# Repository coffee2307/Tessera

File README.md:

# Tessera

## English

### Overview

Tessera is a personal precision motion platform for compact XYZ positioning, alignment, probing, microscopy, and small-scale automation. It combines a parallel-kinematic mechanical structure with closed-loop stepper control, rotary encoders, motion planning, and a serial command interface.

The design aims to provide a low-cost and reproducible motion platform with practical sub-micron positioning capability for laboratory, research, and prototyping workflows. The software stack is divided between embedded firmware and a Python control layer so the hardware can be configured, calibrated, and operated through a clean API.

### Main features

- 3-axis XYZ motion using a parallel-kinematic mechanism
- Closed-loop control with stepper motors and encoder feedback
- Sub-micron positioning for precision alignment and inspection work
- USB serial communication with G-code-style command handling
- Firmware-side path planning and interpolation for smooth motion
- Homing and calibration routines for repeatable setup
- External tool control support for device actuation
- Open hardware and software structure for experimentation and customization

### Project architecture

The repository is organized into several functional domains:

- Mechanical design: CAD and manufacturing files in thiet_ke_co_khi/
- Electronics: PCB and schematics in dien_tu/
- Firmware: embedded C++ controller in phan_mem_nhung/bo_dieu_khien_chuyen_dong_rp/
- Python API: device communication and helper scripts in phan_mem/api_python/
- Documentation: build notes, setup guidance, and BOM in tai_lieu/

### Repository structure

- thiet_ke_co_khi/ - CAD models, assemblies, and mechanical parts
- dien_tu/ - KiCad PCB schematics and board files
- phan_mem_nhung/bo_dieu_khien_chuyen_dong_rp/ - firmware project and embedded source code
- phan_mem_nhung/bo_dieu_khien_chuyen_dong_rp/src/ - C++ firmware implementation
- phan_mem/api_python/ - Python API, utilities, and usage examples
- tai_lieu/ - technical documentation, setup references, and BOM

### Mechanical design

The mechanical platform uses a parallel geometry to achieve compact motion with high stiffness and repeatability. The structure is designed around a three-axis motion system, with linkage and ball-joint behavior tuned for controlled end-effector motion. Mechanical files are stored in the FreeCAD-based construction package and are intended to be modified and adapted for custom builds.

### Electronics design

The electronics layer includes the control board and related hardware configuration. The system relies on stepper drives, encoder interfaces, logic/control circuitry, and power distribution arranged to support the motion controller and its real-time feedback loops. These design files are located under dien_tu/ and provide the hardware reference for the embedded controller.

### Firmware architecture

The firmware is written in C++ and is organized around the real-time device controller. It implements the logic required for motion execution, servo regulation, calibration, and serial communication.

Core firmware responsibilities:

- Kinematic model: workspace and geometry calculations
- Motion controller: command execution and trajectory planning
- Servo control: feedback loops and actuator regulation
- Homing and calibration: initialization and system alignment
- Communication layer: command parsing and response handling

Main firmware components:

- phan_mem_nhung/bo_dieu_khien_chuyen_dong_rp/src/main.cpp - startup and system initialization
- phan_mem_nhung/bo_dieu_khien_chuyen_dong_rp/src/robot.cpp - coordinated device behavior
- phan_mem_nhung/bo_dieu_khien_chuyen_dong_rp/src/dieu_khien_chuyen_dong/ - path planning and movement logic
- phan_mem_nhung/bo_dieu_khien_chuyen_dong_rp/src/dieu_khien_servo/ - closed-loop control loops
- phan_mem_nhung/bo_dieu_khien_chuyen_dong_rp/src/mo_hinh_dong_hoc/ - geometry and kinematic calculations
- phan_mem_nhung/bo_dieu_khien_chuyen_dong_rp/src/hw_config.h - hardware configuration such as pin map and motor settings

### Control and communication model

The system is intended to be commanded over a serial connection. The firmware accepts motion and control instructions and returns status information to the host. This makes it compatible with higher-level control software, automation workflows, and Python-based experimentation.

Typical capabilities include:

- moving to target coordinates
- homing the axes
- enabling or disabling motors
- querying device state
- calibrating joints
- setting tool output values

### Python API

The Python layer wraps the serial connection and exposes a simplified interface for controlling the platform. It is intended to reduce the amount of low-level command handling required when testing motion, calibration, or automated procedures.

Relevant Python files:

- phan_mem/api_python/tessera_api.py
- phan_mem/api_python/vi_du_su_dung.py
- phan_mem/api_python/ve_bieu_do_hieu_chuan.py

The API generally supports:

- connection management
- homing and motion commands
- calibration routines
- device status queries
- asynchronous logging and communication feedback

### Quick start

1. Review the mechanical and electrical documentation in tai_lieu/.
2. Build the hardware according to the project instructions.
3. Adjust the hardware configuration in phan_mem_nhung/bo_dieu_khien_chuyen_dong_rp/src/hw_config.h.
4. Flash the firmware using PlatformIO.
5. Connect the device over serial.
6. Use the Python API or a terminal client to home the platform and begin motion testing.

### Example usage

```python
from phan_mem.api_python.tessera_api import TesseraInterface

api = TesseraInterface(show_communication=True, show_log_messages=True)
api.connect('/dev/ttyACM0')

api.home()
api.move_to(0.0, 0.0, 0.0, f=10)
api.move_to(3.1, 4.1, 5.9, f=26)
api.wait_for_stop()
```

### Notes

- The project is designed for open experimentation and reproducible builds.
- The firmware and mechanical system are the primary technical foundations of the repository.
- The Python layer is meant to simplify communication, testing, calibration, and operational workflows.

---

## Tiếng Việt

### Tổng quan

Tessera là một nền tảng chuyển động XYZ kiểu compact, mã nguồn mở, được thiết kế cho các nhiệm vụ căn chỉnh, dò kiểm tra, kính hiển vi và tự động hóa quy mô nhỏ. Hệ thống này kết hợp cơ cấu cơ khí song song, bộ điều khiển động cơ vòng kín, và giao diện điều khiển thân thiện với Python để tạo ra một giải pháp di chuyển chính xác với chi phí thấp và khả năng tái tạo tốt.

### Tính năng chính

- Chuyển động 3 trục XYZ theo cơ cấu song song
- Điều khiển vòng kín bằng động cơ bước và bộ mã hóa quay
- Khả năng định vị ở mức dưới micromet cho công việc căn chỉnh và kiểm tra
- Giao tiếp qua cổng serial USB với lệnh kiểu G-code
- Lập lịch đường đi và nội suy chuyển động ở phần firmware
- Chức năng homing và hiệu chuẩn để khởi tạo hệ thống lặp lại
- Hỗ trợ điều khiển đầu công cụ ngoài để kích hoạt thiết bị phụ trợ
- Cấu trúc phần cứng và phần mềm mở, dễ tùy biến và thử nghiệm

### Kiến trúc dự án

Kho mã nguồn được tổ chức theo các tầng chức năng chính:

- Thiết kế cơ khí: mô hình CAD và file gia công trong thiet_ke_co_khi/
- Điện tử: bo mạch và sơ đồ trong dien_tu/
- Firmware: bộ điều khiển nhúng C++ trong phan_mem_nhung/bo_dieu_khien_chuyen_dong_rp/
- Python API: giao tiếp thiết bị và script hỗ trợ trong phan_mem/api_python/
- Tài liệu: hướng dẫn xây dựng, thiết lập và BOM trong tai_lieu/

### Cấu trúc thư mục

- thiet_ke_co_khi/ - mô hình CAD, bộ lắp ráp và linh kiện cơ khí
- dien_tu/ - file sơ đồ PCB KiCad và board layout
- phan_mem_nhung/bo_dieu_khien_chuyen_dong_rp/ - mã nguồn firmware và dự án PlatformIO
- phan_mem_nhung/bo_dieu_khien_chuyen_dong_rp/src/ - phần triển khai firmware C++
- phan_mem/api_python/ - API Python, tiện ích và ví dụ sử dụng
- tai_lieu/ - tài liệu kỹ thuật, hướng dẫn lắp đặt và danh mục vật tư

### Thiết kế cơ khí

Cấu trúc cơ khí sử dụng hình học song song để đạt được chuyển động nhỏ gọn, cứng vững và lặp lại tốt. Hệ thống được thiết kế theo mô hình 3 trục với các liên kết và khớp cầu nhằm kiểm soát chuyển động của đầu công cụ. Các file thiết kế cơ khí nằm trong gói CAD FreeCAD và có thể được chỉnh sửa để phù hợp với từng bản dựng cụ thể.

### Thiết kế điện tử

Lớp điện tử bao gồm bo mạch điều khiển và cấu hình phần cứng tương ứng. Hệ thống dùng động cơ bước, giao diện mã hóa, mạch điều khiển logic và phân phối nguồn để hỗ trợ bộ điều khiển chuyển động và vòng phản hồi thời gian thực. Các file này nằm trong dien_tu/ và là tài liệu tham khảo cho phần firmware.

### Kiến trúc firmware

Firmware được viết bằng C++ và tổ chức theo mô hình bộ điều khiển thiết bị thời gian thực. Nó xử lý các nhiệm vụ cần thiết cho việc thực thi chuyển động, điều khiển servo, hiệu chuẩn và giao tiếp serial.

Các trách nhiệm chính của firmware:

- Mô hình động học: tính toán không gian làm việc và hình học
- Bộ điều khiển chuyển động: thực thi lệnh và lập kế hoạch quỹ đạo
- Điều khiển servo: vòng lặp phản hồi và điều chỉnh actuator
- Homing và hiệu chuẩn: khởi tạo và căn chỉnh hệ thống
- Lớp giao tiếp: phân tích lệnh và xử lý phản hồi

Những thành phần quan trọng:

- phan_mem_nhung/bo_dieu_khien_chuyen_dong_rp/src/main.cpp - khởi động và khởi tạo hệ thống
- phan_mem_nhung/bo_dieu_khien_chuyen_dong_rp/src/robot.cpp - hành vi tổng hợp của thiết bị
- phan_mem_nhung/bo_dieu_khien_chuyen_dong_rp/src/dieu_khien_chuyen_dong/ - logic lập kế hoạch đường đi
- phan_mem_nhung/bo_dieu_khien_chuyen_dong_rp/src/dieu_khien_servo/ - vòng lặp điều khiển đóng
- phan_mem_nhung/bo_dieu_khien_chuyen_dong_rp/src/mo_hinh_dong_hoc/ - tính toán hình học và động học
- phan_mem_nhung/bo_dieu_khien_chuyen_dong_rp/src/hw_config.h - cấu hình phần cứng như chân GPIO và cài đặt motor

### Mô hình điều khiển và truyền thông

Hệ thống được thiết kế để điều khiển qua kết nối serial. Firmware nhận lệnh di chuyển và điều khiển từ máy tính và gửi thông tin trạng thái trở lại. Điều này giúp hệ thống tương thích với phần mềm điều khiển cấp cao, quy trình tự động hóa và thử nghiệm dựa trên Python.

Các khả năng điển hình gồm:

- di chuyển đến tọa độ mục tiêu
- homing trục
- bật/tắt động cơ
- truy vấn trạng thái thiết bị
- hiệu chuẩn joint
- đặt giá trị đầu ra của công cụ

### Python API

Lớp Python đóng gói kết nối serial và cung cấp giao diện đơn giản để điều khiển hệ thống. Mục tiêu là giảm khối lượng xử lý lệnh mức thấp khi kiểm tra chuyển động, hiệu chuẩn hoặc quy trình tự động hóa.

Các file Python quan trọng:

- phan_mem/api_python/tessera_api.py
- phan_mem/api_python/vi_du_su_dung.py
- phan_mem/api_python/ve_bieu_do_hieu_chuan.py

API thường hỗ trợ:

- quản lý kết nối
- lệnh homing và di chuyển
- chức năng hiệu chuẩn
- truy vấn trạng thái thiết bị
- log giao tiếp và phản hồi liên tục

### Bắt đầu nhanh

1. Đọc tài liệu cơ khí và điện tử trong tai_lieu/
2. Lắp ráp phần cứng theo hướng dẫn của dự án
3. Điều chỉnh cấu hình phần cứng trong phan_mem_nhung/bo_dieu_khien_chuyen_dong_rp/src/hw_config.h
4. Nạp firmware bằng PlatformIO
5. Kết nối thiết bị qua serial
6. Dùng Python API hoặc client terminal để homing trục và bắt đầu kiểm tra chuyển động

### Ví dụ sử dụng

```python
from phan_mem.api_python.tessera_api import TesseraInterface

api = TesseraInterface(show_communication=True, show_log_messages=True)
api.connect('/dev/ttyACM0')

api.home()
api.move_to(0.0, 0.0, 0.0, f=10)
api.move_to(3.1, 4.1, 5.9, f=26)
api.wait_for_stop()
```

### Lưu ý

- Dự án này thích hợp cho thử nghiệm mở và bản dựng có thể tái sản xuất.
- Firmware và hệ thống cơ khí là nền tảng kỹ thuật chính của kho mã nguồn.
- Lớp Python nhằm đơn giản hóa giao tiếp, thử nghiệm, hiệu chuẩn và quy trình vận hành.

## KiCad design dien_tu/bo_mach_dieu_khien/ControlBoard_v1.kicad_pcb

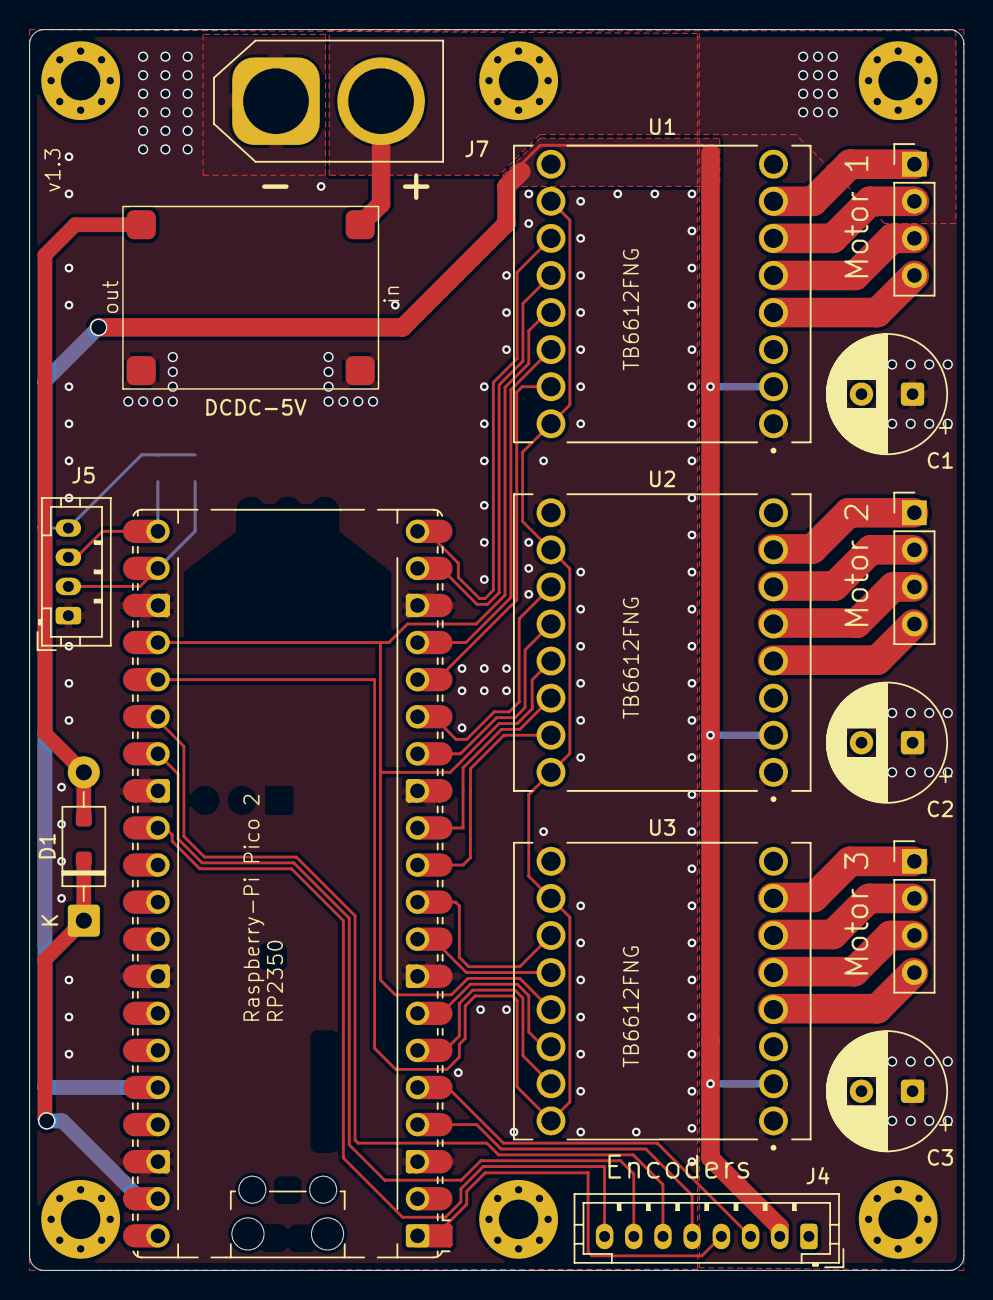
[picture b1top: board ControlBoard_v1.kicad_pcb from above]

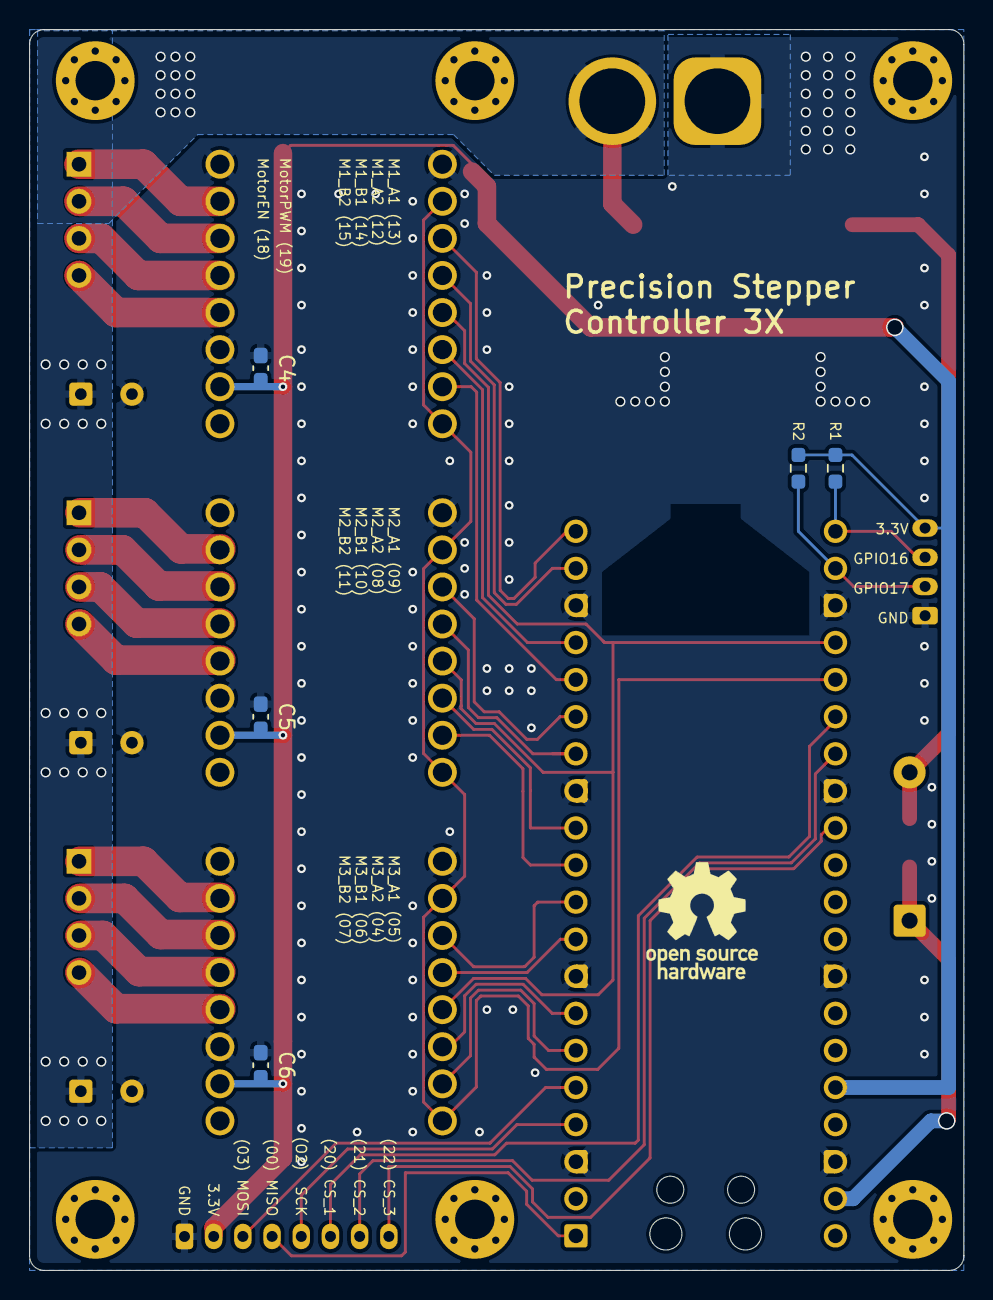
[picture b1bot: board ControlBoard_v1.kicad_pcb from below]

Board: 2 copper layers, 64.0 x 85.0 mm, 27 parts (6 on the bottom side), 39 nets.

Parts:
A1: RaspberryPi_Pico; RaspberryPi_Pico_Common_Unspecified
C1, C2, C3: C_Polarized; CP_Radial_D8.0mm_P3.50mm
C4, C5, C6: C; C_0603_1608Metric_Pad1.08x0.95mm_HandSolder
D1: 1N5819; D_DO-41_SOD81_P10.16mm_Horizontal
D2: PMEG4010; D_SOD-123F
H1, H2, H3, H4, H5, H6: MountingHole_Pad; MountingHole_2.7mm_M2.5_Pad_Via
J1: Motor1; PinHeader_1x04_P2.54mm_Vertical
J2: Motor2; PinHeader_1x04_P2.54mm_Vertical
J3: Motor3; PinHeader_1x04_P2.54mm_Vertical
J4: Encoder; JST_PH_B8B-PH-K_1x08_P2.00mm_Vertical
J5: I2C; JST_PH_B4B-PH-K_1x04_P2.00mm_Vertical
J7: Power; AMASS_XT60-M_1x02_P7.20mm_Vertical
R1, R2: 4K7; R_0603_1608Metric_Pad0.98x0.95mm_HandSolder
U1, U2, U3: ROB-14450; MODULE_ROB-14450
U4: DCDC_Converter; DCDC_17mmx12mm

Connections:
+3.3V: A1.36 (3V3), C4.1, C5.1, C6.1, J4.2, J5.4, R1.1, R2.1, U1.2 (VCC), U2.2 (VCC), U3.2 (VCC)
+5V: A1.39 (VSYS), D1.1 (K), D2.1 (K)
+12V: C1.1, C2.1, C3.1, J7.2, U1.1 (VM), U2.1 (VM), U3.1 (VM), U4.2 (IN+)
/Encoder1_CS: A1.26 (GPIO20), J4.6
/Encoder2_CS: A1.27 (GPIO21), J4.7
/Encoder3_CS: A1.29 (GPIO22), J4.8
/Encoder_MISO: A1.1 (GPIO0), J4.4
/Encoder_MOSI: A1.5 (GPIO3), J4.3
/Encoder_SCK: A1.4 (GPIO2), J4.5
/I2C_SCL: A1.21 (GPIO16), J5.3, R1.2
/I2C_SDA: A1.22 (GPIO17), J5.2, R2.2
/Motor1_A1: A1.17 (GPIO13), U1.14 (AI1)
/Motor1_A2: A1.16 (GPIO12), U1.15 (AI2)
/Motor1_B1: A1.19 (GPIO14), U1.12 (BI1)
/Motor1_B2: A1.20 (GPIO15), U1.11 (BI2)
/Motor2_A1: A1.12 (GPIO9), U2.14 (AI1)
/Motor2_A2: A1.11 (GPIO8), U2.15 (AI2)
/Motor2_B1: A1.14 (GPIO10), U2.12 (BI1)
/Motor2_B2: A1.15 (GPIO11), U2.11 (BI2)
/Motor3_A1: A1.7 (GPIO5), U3.14 (AI1)
/Motor3_A2: A1.6 (GPIO4), U3.15 (AI2)
/Motor3_B1: A1.9 (GPIO6), U3.12 (BI1)
/Motor3_B2: A1.10 (GPIO7), U3.11 (BI2)
/MotorEN: A1.24 (GPIO18), U1.13 (STBY), U2.13 (STBY), U3.13 (STBY)
/MotorPWM: A1.25 (GPIO19), U1.10 (PWMB), U1.16 (PWMA), U2.10 (PWMB), U2.16 (PWMA), U3.10 (PWMB), U3.16 (PWMA)
GND: A1.3 (GND), A1.8 (GND), A1.13 (GND), A1.18 (GND), A1.23 (GND), A1.28 (GND), A1.33 (AGND), A1.38 (GND), C1.2, C2.2, C3.2, C4.2, C5.2, C6.2, J4.1, J5.1, J7.1, U1.3 (GND), U1.8 (GND), U1.9 (GND), U2.3 (GND), U2.8 (GND), U2.9 (GND), U3.3 (GND), U3.8 (GND), U3.9 (GND), U4.1 (IN-), U4.3 (OUT-)
unnamed: D1.2 (A), D2.2 (A), U4.4 (OUT+)
unnamed: J1.1, U1.7 (B01)
unnamed: J1.2, U1.6 (B02)
unnamed: J1.3, U1.5 (A02)
unnamed: J1.4, U1.4 (A01)
unnamed: J2.1, U2.7 (B01)
unnamed: J2.2, U2.6 (B02)
unnamed: J2.3, U2.5 (A02)
unnamed: J2.4, U2.4 (A01)
unnamed: J3.1, U3.7 (B01)
unnamed: J3.2, U3.6 (B02)
unnamed: J3.3, U3.5 (A02)
unnamed: J3.4, U3.4 (A01)

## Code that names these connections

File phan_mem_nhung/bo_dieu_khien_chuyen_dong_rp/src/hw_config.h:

#pragma once
#include "tien_ich/math_constants.h"

// #define DEMO_MODE

//--- MOTORS ------------------------------------------------------------------

// motor pole pair count
//  * 100 for 0.9deg stepper motors
//  * 50  for 1.8deg stepper motors
constexpr float MOTOR1_POLE_PAIRS = 50;
constexpr float MOTOR2_POLE_PAIRS = 50;
constexpr float MOTOR3_POLE_PAIRS = 50;

// max current factor in range [0..1]. Lower values reduce pwm resolution so a
// value above 0.4 is recommended.
constexpr float MOTOR_MAX_CURRENT_FACTOR = 0.6f;

//--- ENCODERS ----------------------------------------------------------------

// Conversion factor from encoder angle (one 2pi period every two magnets) to rotor angle.
// Used when the system can not rely on calibration data being present (e.g. during homing)
constexpr float ENCODER_MAGNET_PITCH = 3.0f;    // [mm]
constexpr float ENCODER_MAGNET_RADIUS = 30.0f;  // [mm]
constexpr float ENCODER_ANGLE_TO_ROTOR_ANGLE = (ENCODER_MAGNET_PITCH*2.0f) / 
                                               (ENCODER_MAGNET_RADIUS * Constants::TWO_PI_F);
											   
// enables error checking for encoders (slow) - useful for debugging
// Note: some chips seem to return always a crc of 0 producing massiv false errors       
constexpr bool ENABLE_ENCODER_CRC = false;

//--- HOMING ------------------------------------------------------------------

constexpr float HOMING_VELOCITY   = 1.0f;        // rad per s
constexpr float HOMING_CURRENT    = 0.15f;       // range 0..1
// NOT IMPLEMENTED YET: constexpr float HOMING_FINISH_POS = 0.5f;        // in rad

//--- CALIBRATION -------------------------------------------------------------

// degrees from home position
constexpr float CALIBRATION_RANGE = 83; 

// velocity of the magnetic field during calibration (lower is more accurate)
constexpr float CALIBRATION_FIELD_VELOCITY = 20.0f; 

// size of the calibration lookup table
constexpr int ENCODER_LUT_SIZE = 256;

//--- CLOSED LOOP CONTROL -----------------------------------------------------

// position controller 
constexpr float POS_KP = 60.0f;
constexpr float POS_KI = 30000.0f;

// velocity controller
constexpr float VEL_LOWPASS_TC = 0.004f;
constexpr float VEL_KP = 0.2f;
constexpr float VEL_KI = 90.0f;

//--- KINEMATIC ---------------------------------------------------------------

// Kinematic Parameters are defined kinematic_modes/kinematic_model_delta3d.cpp

// NUM_JOINTS and NUM_TOOLS are defined in 'path_segment.h'. Note that changing
// the number of joints requires changing the kinematic model accordingly and
// also requires the initialization of the correct number of 'RobotJoint' objects
// in the Robtos init method.

//--- PINS --------------------------------------------------------------------

#define JOINT_READY_OVERRIDE

// #define SINGLE_AXIS_BOARD
#ifndef SINGLE_AXIS_BOARD
  // Pins for 3Axis Board
  // #define PIN_BUILTIN_LED 23 // RP2040 pico clone
  // #define PIN_USER_BUTTON 24 // RP2040 pico clone
  #define PIN_BUILTIN_LED 25

  #define PIN_M1_PWM_A_POS  13
  #define PIN_M1_PWM_A_NEG  12
  #define PIN_M1_PWM_B_POS  14
  #define PIN_M1_PWM_B_NEG  15

  #define PIN_M2_PWM_A_POS  9
  #define PIN_M2_PWM_A_NEG  8
  #define PIN_M2_PWM_B_POS  10
  #define PIN_M2_PWM_B_NEG  11

  #define PIN_M3_PWM_A_POS  5
  #define PIN_M3_PWM_A_NEG  4
  #define PIN_M3_PWM_B_POS  6
  #define PIN_M3_PWM_B_NEG  7


  #define PIN_MOTOR_EN      18
  #define PIN_MOTOR_PWMAB   19

  #define PIN_ENCODER1_CS 20
  #define PIN_ENCODER2_CS 21
  #define PIN_ENCODER3_CS 22
  #define PIN_ENCODER_SCK 2
  #define PIN_ENCODER_MISO 0
  #define PIN_ENCODER_MOSI 3

  #define PIN_TOOL1 16
  #define PIN_TOOL2 17

#else
  // Single Axis Board
  #define PIN_BUILTIN_LED 16
  #define PIN_USER_BUTTON 24

  #define PIN_M1_PWM_A_POS  13
  #define PIN_M1_PWM_A_NEG  12
  #define PIN_M1_PWM_B_POS  14
  #define PIN_M1_PWM_B_NEG  15

  #define PIN_M2_PWM_A_POS  9
  #define PIN_M2_PWM_A_NEG  8
  #define PIN_M2_PWM_B_POS  10
  #define PIN_M2_PWM_B_NEG  11

  #define PIN_M3_PWM_A_POS  5
  #define PIN_M3_PWM_A_NEG  4
  #define PIN_M3_PWM_B_POS  6
  #define PIN_M3_PWM_B_NEG  7


  #define PIN_MOTOR_EN      18
  #define PIN_MOTOR_PWMAB   19

  #define PIN_ENCODER1_CS 20
  #define PIN_ENCODER2_CS 21
  #define PIN_ENCODER3_CS 22
  #define PIN_ENCODER_SCK 2
  #define PIN_ENCODER_MISO 0
  #define PIN_ENCODER_MOSI 3
#endif
